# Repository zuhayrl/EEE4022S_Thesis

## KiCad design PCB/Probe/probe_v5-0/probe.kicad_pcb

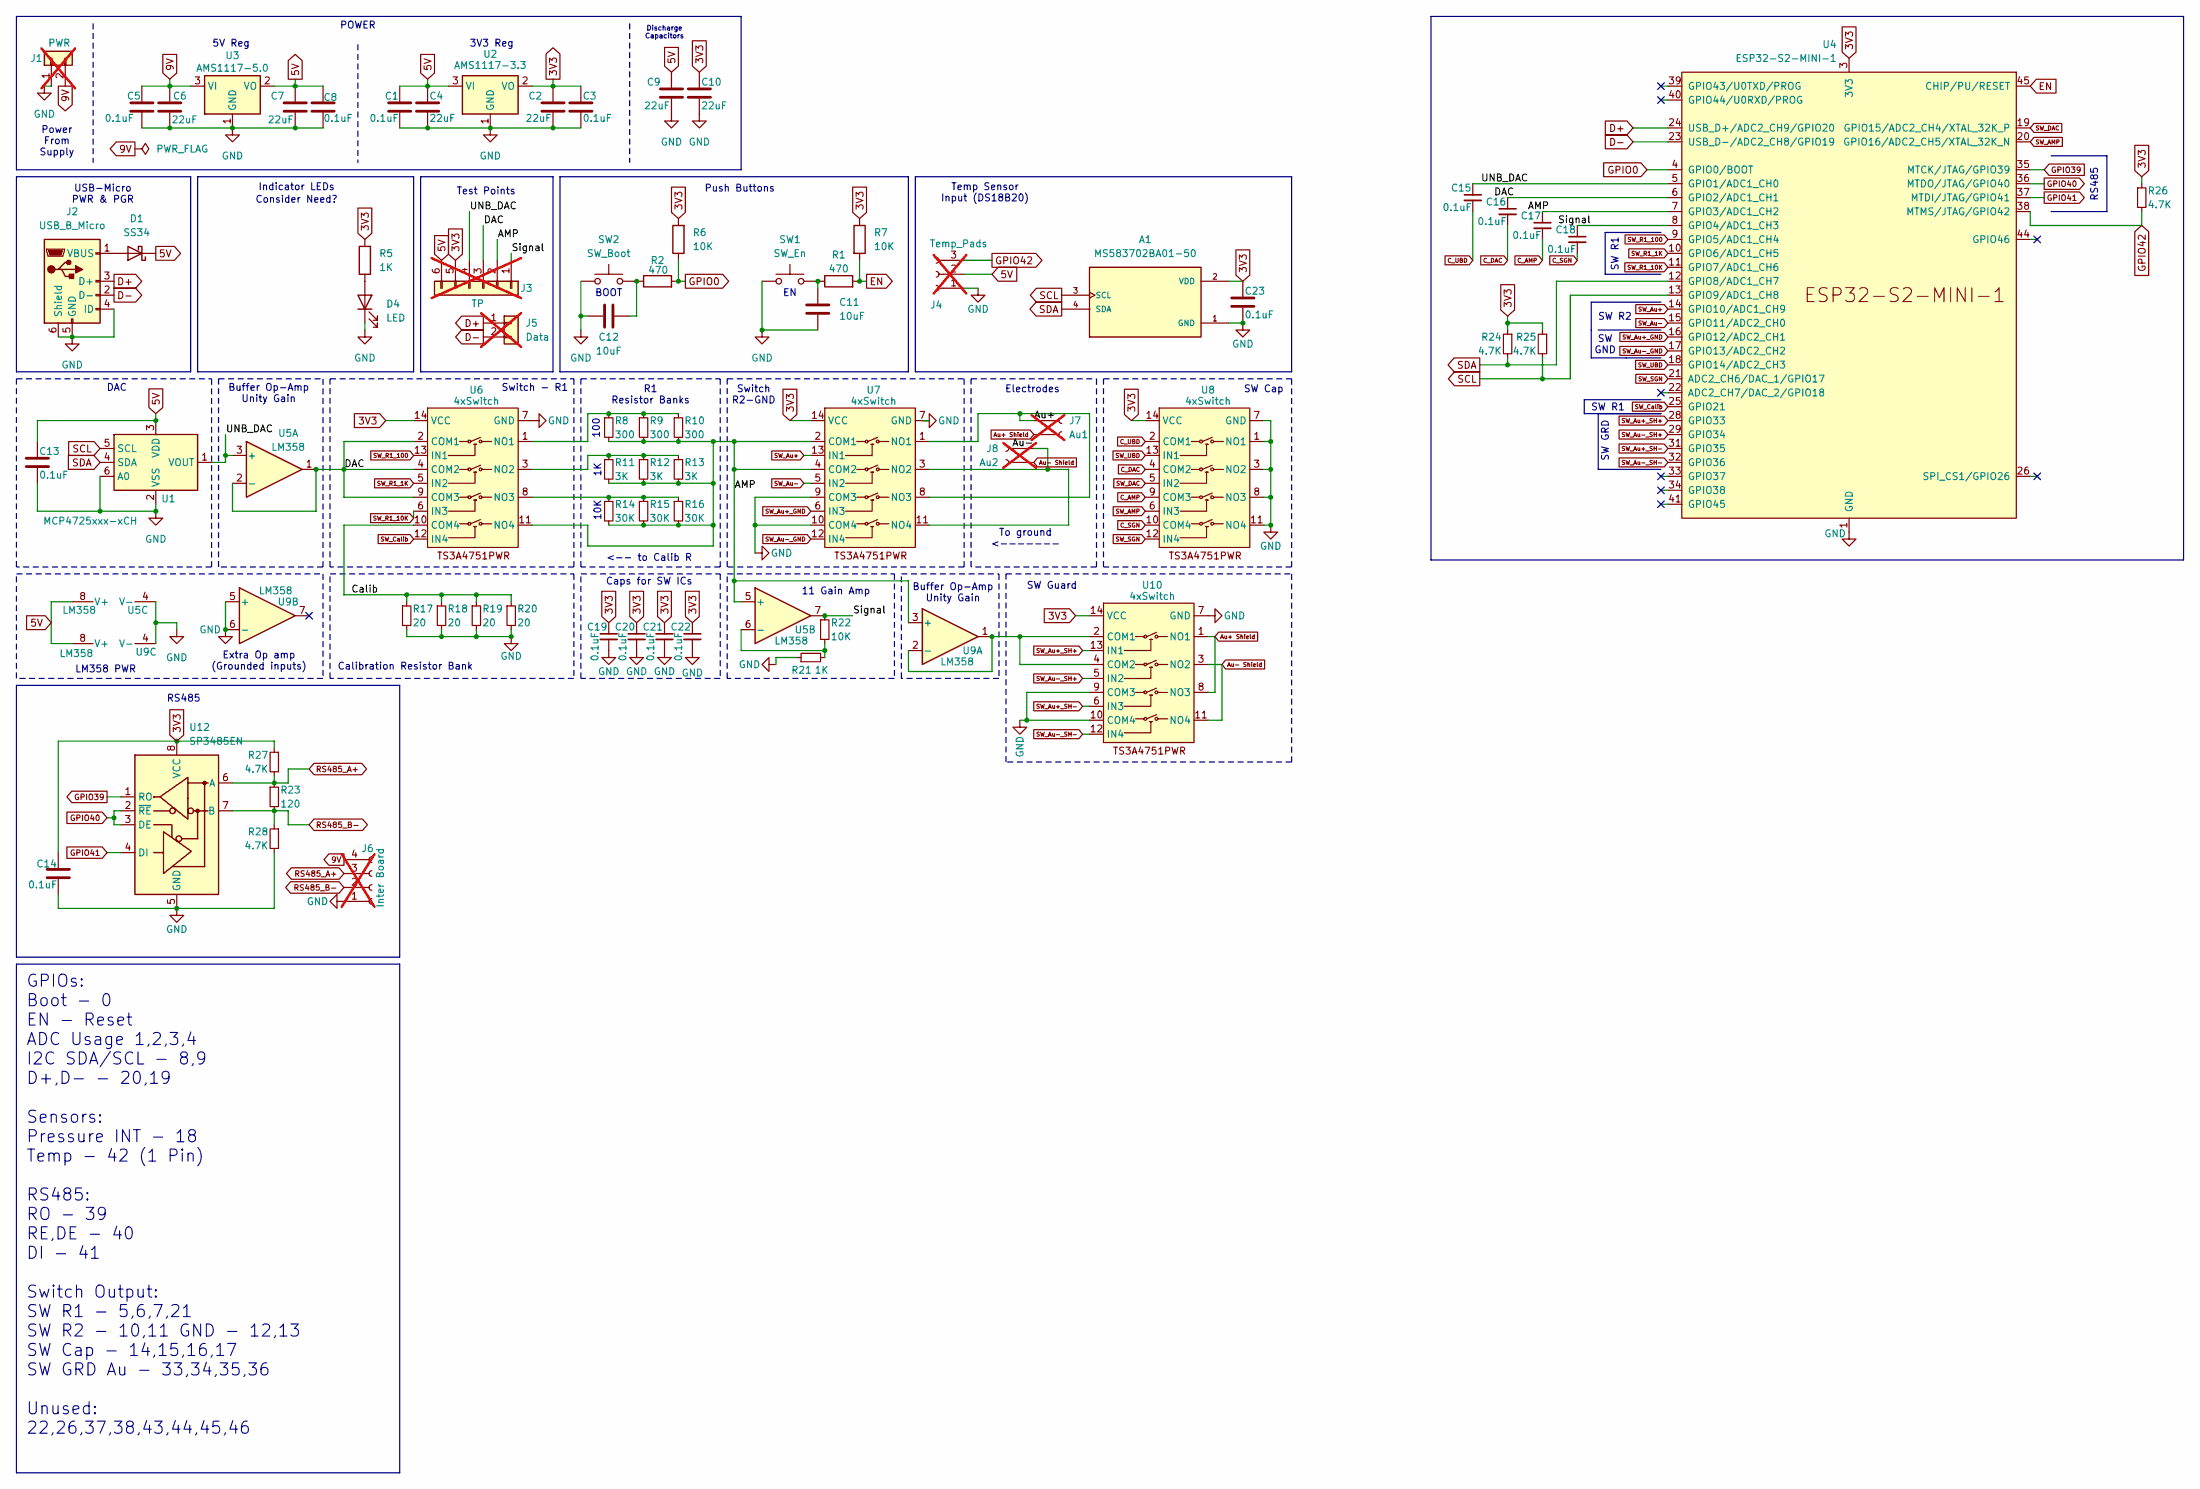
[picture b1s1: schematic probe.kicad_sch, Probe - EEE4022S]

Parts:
A1: MS583702BA01-50; XDCR_MS583702BA01-50; PARTREV A8; JLC Part no. C5785272
C1, C3, C5, C8, C13, C14, C15, C16, C17, C18, C19, C20, C21, C22, C23: 0.1uF; C_0402_1005Metric; JLC Part no. C1525
C2, C4, C6, C7, C9, C10: 22uF; C_1206_3216Metric; JLC Part no. C12891
C11, C12: 10uF; C_0603_1608Metric; JLC Part no. C19702
D1: SS34; D_SMA; JLC Part no. C8678
D4: LED; LED_0603_1608Metric; JLC Part no. C2286
J1: PWR; PinHeader_1x02_P2.54mm_Vertical; not fitted
J2: USB_B_Micro; SHOUHAN_MICROXNJ_Edited; JLC Part no. C404969
J3: TP; PinHeader_1x06_P2.54mm_Vertical; not fitted
J4: Temp_Pads; 3-Wire Solder Pads; not fitted
J5: Data; PinHeader_1x02_P2.54mm_Vertical; not fitted
J6: Inter Board; PinHeader_1x04_P2.54mm_Vertical; not fitted
J7: Au1; Au_Electrode_edited_1; not fitted
J8: Au2; Au_Electrode_edited_1; not fitted
R1, R2: 470; R_0603_1608Metric; JLC Part no. C23179
R5, R21: 1K; R_0603_1608Metric; JLC Part no. C21190
R6, R7, R22: 10K; R_0603_1608Metric; JLC Part no. C25804
R8, R9, R10: 300; R_0603_1608Metric; JLC Part no. C23025
R11, R12, R13: 3K; R_0603_1608Metric; JLC Part no. C4211
R14, R15, R16: 30K; R_0603_1608Metric; JLC Part no. C22984
R17, R18, R19, R20: 20; R_0603_1608Metric; JLC Part no. C22950
R23: 120; R_0603_1608Metric; JLC Part no. C22787
R24, R25, R26, R27, R28: 4.7K; R_0603_1608Metric; JLC Part no. C23162
SW1: SW_En; SW_TS-1088-AR02016; JLC Part no. C720477
SW2: SW_Boot; SW_TS-1088-AR02016; JLC Part no. C720477
U1: MCP4725xxx-xCH; SOT-23-6; JLC Part no. C144198
U2: AMS1117-3.3; SOT-223-3_TabPin2; JLC Part no. C6186
U3: AMS1117-5.0; SOT-223-3_TabPin2; JLC Part no. C6187
U4: ESP32-S2-MINI-1; JLC Part no. C3013906
U5, U9: LM358; SOIC-8_3.9x4.9mm_P1.27mm; JLC Part no. C7950
U6, U7, U8, U10: 4xSwitch; TSSOP-14_4.4x5mm_P0.65mm; JLC Part no. C128399
U12: SP3485EN; SOIC-8_3.9x4.9mm_P1.27mm; JLC Part no. C8963

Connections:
3V3: A1.2 (VDD), C2.1, C3.1, C10.1, C14.1, C19.1, C20.1, C21.1, C22.1, C23.1, J3.5, R5.2, R6.2, R7.1, R24.1, R25.1, R26.1, R27.1, U2.2 (VO), U4.3 (3V3), U6.14 (VCC), U7.14 (VCC), U8.14 (VCC), U10.14 (VCC), U12.8 (VCC)
5V: C1.1, C4.1, C7.1, C8.1, C9.1, C13.1, D1.1 (K), J3.6, J4.2, U1.3 (VDD), U2.3 (VI), U3.2 (VO), U5.8 (V+), U9.8 (V+)
9V: C5.1, C6.1, J1.2, J6.4, U3.3 (VI)
/AMP: C17.1, J3.2, R8.2, R9.2, R10.2, R11.2, R12.2, R13.2, R14.2, R15.2, R16.2, U4.7 (GPIO3/ADC1_CH2), U5.5 (+), U6.11 (NO4), U7.2 (COM1), U7.4 (COM2), U9.3 (+)
/Au+: J7.1, U7.1 (NO1), U7.8 (NO3)
/Au-: J8.1, U7.3 (NO2), U7.11 (NO4)
/Calib: R17.1, R18.1, R19.1, R20.1, U6.10 (COM4)
/DAC: C16.1, J3.3, U4.6 (GPIO2/ADC1_CH1), U5.1, U5.2 (-), U6.2 (COM1), U6.4 (COM2), U6.9 (COM3)
/Signal: C18.1, J3.1, R22.1, U4.8 (GPIO4/ADC1_CH3), U5.7
/UNB_DAC: C15.1, J3.4, U1.1 (VOUT), U4.5 (GPIO1/ADC1_CH0), U5.3 (+)
Au+ Shield: J7.2, U10.1 (NO1), U10.8 (NO3)
Au- Shield: J8.2, U10.3 (NO2), U10.11 (NO4)
C_AMP: C17.2, U8.9 (COM3)
C_DAC: C16.2, U8.4 (COM2)
C_SGN: C18.2, U8.10 (COM4)
C_UBD: C15.2, U8.2 (COM1)
D+: J2.3 (D+), J5.1, U4.24 (USB_D+/ADC2_CH9/GPIO20)
D-: J2.2 (D-), J5.2, U4.23 (USB_D-/ADC2_CH8/GPIO19)
EN: R1.2, R7.2, U4.45 (CHIP/PU/RESET)
GND: A1.1 (GND), C1.2, C2.2, C3.2, C4.2, C5.2, C6.2, C7.2, C8.2, C9.2, C10.2, C11.2, C12.2, C13.2, C14.2, C19.2, C20.2, C21.2, C22.2, C23.2, D4.1 (K), J1.1, J2.4 (ID), J2.5 (GND), J2.6 (Shield), J4.1, J6.1, R17.2, R18.2, R19.2, R20.2, R21.1, R28.2, SW1.1, SW2.1, U1.2 (VSS), U1.6 (A0), U2.1 (GND), U3.1 (GND), U4.1 (GND), U4.2 (GND), U4.30 (GND), U4.42 (GND), U4.43 (GND), U4.46 (GND), U4.47 (GND), U4.48 (GND), U4.49 (GND), U4.50 (GND), U4.51 (GND), U4.52 (GND), U4.53 (GND), U4.54 (GND), U4.55 (GND), U4.56 (GND), U4.57 (GND), U4.58 (GND), U4.59 (GND), U4.60 (GND), U4.61 (GND), U4.62 (GND), U4.63 (GND), U4.64 (GND), U4.65 (GND), U5.4 (V-), U6.7 (GND), U7.7 (GND), U7.9 (COM3), U7.10 (COM4), U8.1 (NO1), U8.3 (NO2), U8.7 (GND), U8.8 (NO3), U8.11 (NO4), U9.4 (V-), U9.5 (+), U9.6 (-), U10.7 (GND), U10.9 (COM3), U10.10 (COM4), U12.5 (GND)
GPIO0: R2.2, R6.1, U4.4 (GPIO0/BOOT)
GPIO39: U4.35 (MTCK/JTAG/GPIO39), U12.1 (RO)
GPIO40: U4.36 (MTDO/JTAG/GPIO40), U12.2 (~RE), U12.3 (DE)
GPIO41: U4.37 (MTDI/JTAG/GPIO41), U12.4 (DI)
GPIO42: J4.3, R26.2, U4.38 (MTMS/JTAG/GPIO42)
unnamed: C11.1, R1.1, SW1.2
unnamed: C12.1, R2.1, SW2.2
unnamed: D1.2 (A), J2.1 (VBUS)
unnamed: D4.2 (A), R5.1
unnamed: R21.2, R22.2, U5.6 (-)
unnamed: R8.1, R9.1, R10.1, U6.1 (NO1)
unnamed: R11.1, R12.1, R13.1, U6.3 (NO2)
unnamed: R14.1, R15.1, R16.1, U6.8 (NO3)
unnamed: U9.1, U9.2 (-), U10.2 (COM1), U10.4 (COM2)
RS485_A+: J6.3, R23.1, R27.2, U12.6 (A)
RS485_B-: J6.2, R23.2, R28.1, U12.7 (B)
SCL: A1.3 (SCL), R25.2, U1.5 (SCL), U4.13 (GPIO9/ADC1_CH8)
SDA: A1.4 (SDA), R24.2, U1.4 (SDA), U4.12 (GPIO8/ADC1_CH7)
SW_AMP: U4.20 (GPIO16/ADC2_CH5/XTAL_32K_N), U8.6 (IN3)
SW_Au+: U4.14 (GPIO10/ADC1_CH9), U7.13 (IN1)
SW_Au+_GND: U4.16 (GPIO12/ADC2_CH1), U7.6 (IN3)
SW_Au+_SH+: U4.28 (GPIO33), U10.13 (IN1)
SW_Au+_SH-: U4.31 (GPIO35), U10.6 (IN3)
SW_Au-: U4.15 (GPIO11/ADC2_CH0), U7.5 (IN2)
SW_Au-_GND: U4.17 (GPIO13/ADC2_CH2), U7.12 (IN4)
SW_Au-_SH+: U4.29 (GPIO34), U10.5 (IN2)
SW_Au-_SH-: U4.32 (GPIO36), U10.12 (IN4)
SW_Calib: U4.25 (GPIO21), U6.12 (IN4)
SW_DAC: U4.19 (GPIO15/ADC2_CH4/XTAL_32K_P), U8.5 (IN2)
SW_R1_1K: U4.10 (GPIO6/ADC1_CH5), U6.5 (IN2)
SW_R1_10K: U4.11 (GPIO7/ADC1_CH6), U6.6 (IN3)
SW_R1_100: U4.9 (GPIO5/ADC1_CH4), U6.13 (IN1)
SW_SGN: U4.21 (ADC2_CH6/DAC_1/GPIO17), U8.12 (IN4)
SW_UBD: U4.18 (GPIO14/ADC2_CH3), U8.13 (IN1)

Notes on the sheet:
GPIOs: Boot - 0 EN - Reset ADC Usage 1,2,3,4 I2C SDA/SCL - 8,9 D+,D- - 20,19 Sensors: Pressure INT - 18 Temp - 42 (1 Pin) RS485: RO - 39 RE,DE - 40 DI - 41 Switch Output: SW R1 - 5,6,7,21 SW R2 - 10,11 GND - 12,13 SW Cap - 14,15,16,17 SW GRD Au - 33,34,35,36 Unused: 22,26,37,38,43,44,45,46
Extra Op amp (Grounded inputs)
Switch - R1
Calibration Resistor Bank
BOOT
SW R1
Test Points
5V Reg
POWER
SW GND
Discharge Capacitors
SW Cap
3V3 Reg
LM358 PWR
USB-Micro PWR & PGR
To ground <-------
Push Buttons
SW R2
DAC
Consider Need?
10K
SW GRD
Electrodes
RS485
Buffer Op-Amp Unity Gain
Temp Sensor Input (DS18B20)
100
Indicator LEDs
Switch R2-GND
SW Guard
Caps for SW ICs
<-- to Calib R
Power From Supply
11 Gain Amp
R1 Resistor Banks

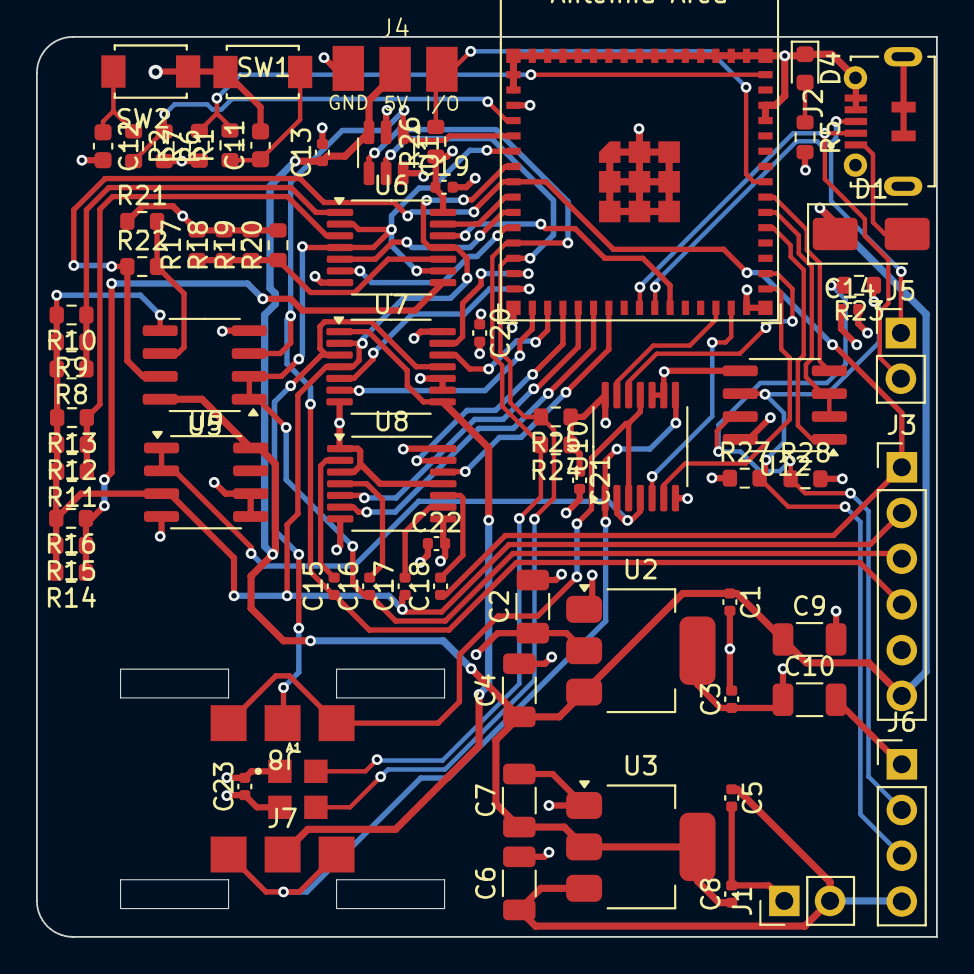
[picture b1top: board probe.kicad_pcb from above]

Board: 4 copper layers, 50.0 x 50.0 mm, 73 parts (0 on the bottom side), 54 nets.

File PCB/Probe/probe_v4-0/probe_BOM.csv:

Comment,Designator,Footprint,JLC Part #
0.1uF,"C1,C3,C5,C8,C13,C14,C15,C16,C17,C18,C19,C20,C21,C22,C23",Capacitor_SMD:C_0402_1005Metric,C1525
22uF,"C2,C4,C6,C7,C9,C10",Capacitor_SMD:C_1206_3216Metric,C12891
10uF,"C11,C12",Capacitor_SMD:C_0603_1608Metric,C19702
SS34,D1,Diode_SMD:D_SMA,C8678
LED,D4,LED_SMD:LED_0603_1608Metric,C2286
PWR,J1,Connector_PinHeader_2.54mm:PinHeader_1x02_P2.54mm_Vertical,
USB_B_Micro,J2,ThesisLib:SHOUHAN_MICROXNJ_Edited,C404969
TP,J3,Connector_PinHeader_2.54mm:PinHeader_1x06_P2.54mm_Vertical,
Temp_Pads,J4,ThesisLib:3-Wire Solder Pads,
Data,J5,Connector_PinHeader_2.54mm:PinHeader_1x02_P2.54mm_Vertical,
Inter Board,J6,Connector_PinHeader_2.54mm:PinHeader_1x04_P2.54mm_Vertical,
Au1,J7,ThesisLib:Au_Electrode_edited_1,
Au2,J8,ThesisLib:Au_Electrode_edited_1,
470,"R1,R2",Resistor_SMD:R_0603_1608Metric,
1K,"R5,R21",Resistor_SMD:R_0603_1608Metric,C21190
10K,"R6,R7,R22",Resistor_SMD:R_0603_1608Metric,C25804
300,"R8,R9,R10",Resistor_SMD:R_0603_1608Metric,C23025
3K,"R11,R12,R13",Resistor_SMD:R_0603_1608Metric,C4211
30K,"R14,R15,R16",Resistor_SMD:R_0603_1608Metric,C22984
20,"R17,R18,R19,R20",Resistor_SMD:R_0603_1608Metric,C22950
120,R23,Resistor_SMD:R_0603_1608Metric,C22787
4.7K,"R24,R25,R26,R27,R28",Resistor_SMD:R_0603_1608Metric,C23162
SW_En,SW1,ThesisLib:SW_TS-1088-AR02016,C720477
SW_Boot,SW2,ThesisLib:SW_TS-1088-AR02016,C720477
MCP4725xxx-xCH,U1,Package_TO_SOT_SMD:SOT-23-6,C144198
AMS1117-3.3,U2,Package_TO_SOT_SMD:SOT-223-3_TabPin2,C6186
AMS1117-5.0,U3,Package_TO_SOT_SMD:SOT-223-3_TabPin2,C6187
ESP32-S2-MINI-1,U4,PCM_Espressif:ESP32-S2-MINI-1,C3013906
LM358,"U5,U9",Package_SO:SOIC-8_3.9x4.9mm_P1.27mm,C7950
4xSwitch,"U6,U7,U8,U10",Package_SO:TSSOP-14_4.4x5mm_P0.65mm,C128399
SP3485EN,U12,Package_SO:SOIC-8_3.9x4.9mm_P1.27mm,C8963
LPS28DFW,U13,ThesisLib:CCLGA-7L,C3263277

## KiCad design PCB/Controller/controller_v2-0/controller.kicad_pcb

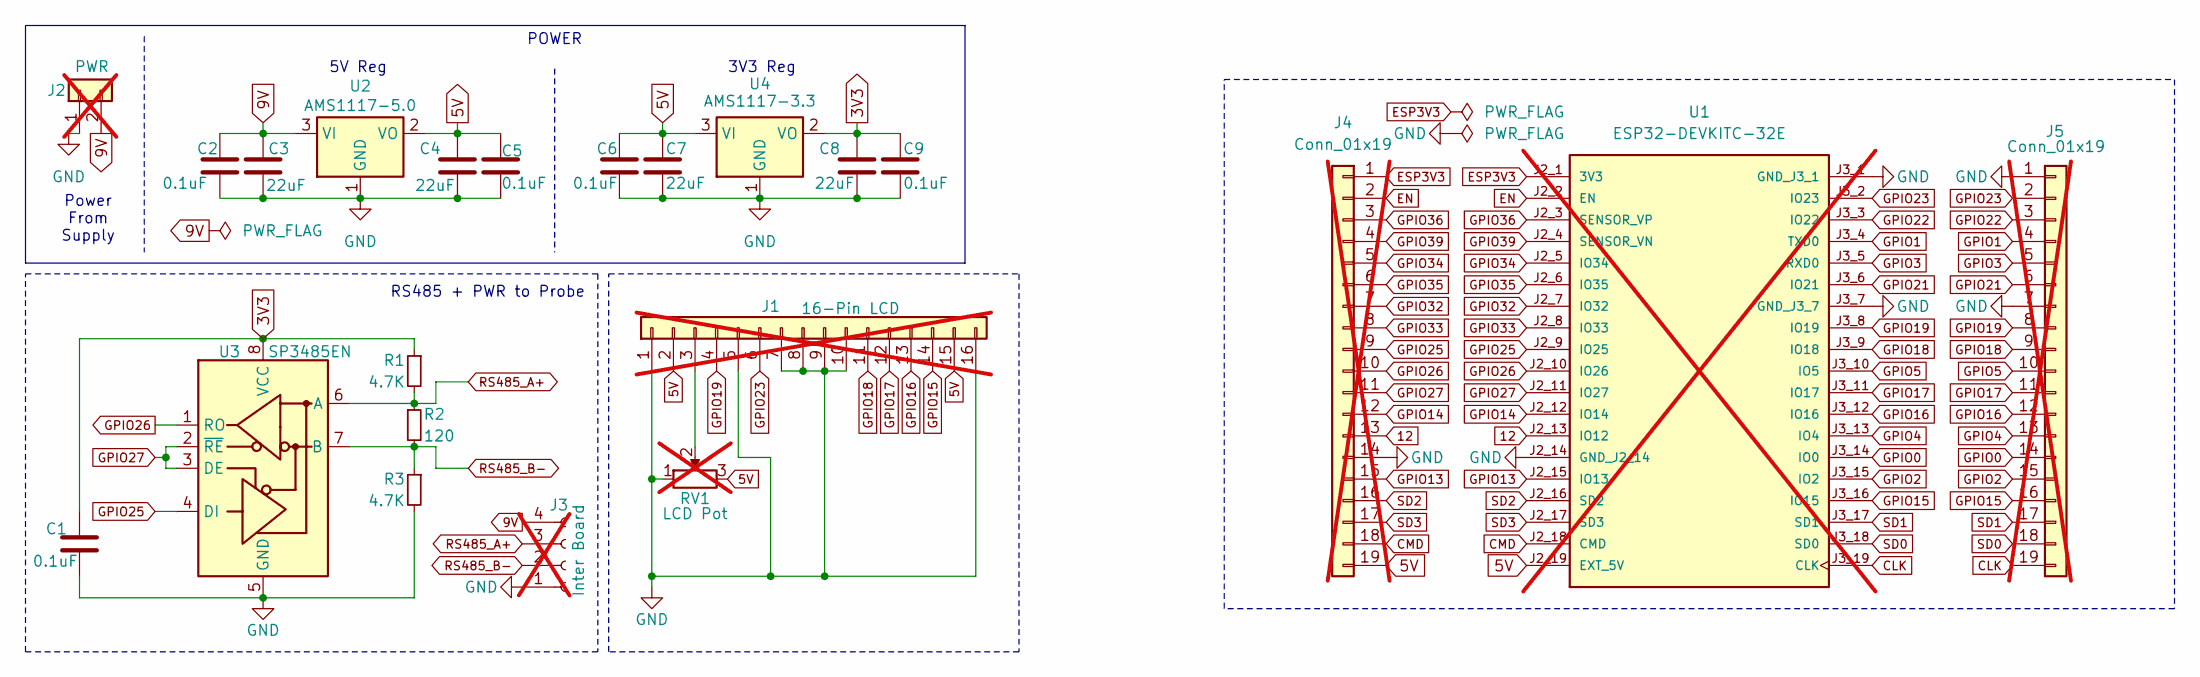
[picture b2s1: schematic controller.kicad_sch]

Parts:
C1, C2, C5, C6, C9: 0.1uF; C_0402_1005Metric; JLCPCB Part No. C1525
C3, C4, C7, C8: 22uF; C_1206_3216Metric; JLCPCB Part No. C12891
J1: 16-Pin LCD; PinSocket_1x16_P2.54mm_Vertical; not fitted
J2: PWR; PinHeader_1x02_P2.54mm_Vertical; not fitted
J3: Inter Board; PinHeader_1x04_P2.54mm_Vertical; not fitted
J4, J5: Conn_01x19; PinHeader_1x19_P2.54mm_Vertical; not fitted
R1, R3: 4.7K; R_0603_1608Metric; JLCPCB Part No. C23162
R2: 120; R_0603_1608Metric; JLCPCB Part No. C22787
RV1: LCD Pot; 10KPot; not fitted
U1: ESP32-DEVKITC-32E; MODULE_ESP32-DEVKITC-32E-Edited2; PARTREV 1.4; not fitted
U2: AMS1117-5.0; SOT-223-3_TabPin2; JLCPCB Part No. C6187
U3: SP3485EN; SOIC-8_3.9x4.9mm_P1.27mm; JLCPCB Part No. C8963
U4: AMS1117-3.3; SOT-223-3_TabPin2; JLCPCB Part No. C6186

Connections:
3V3: C1.1, C8.1, C9.1, R1.1, U3.8 (VCC), U4.2 (VO)
5V: C4.1, C5.1, C6.1, C7.1, J1.2, J1.15, J4.19, RV1.3, U1.J2_19 (EXT_5V), U2.2 (VO), U4.3 (VI)
9V: C2.1, C3.1, J2.2, J3.4, U2.3 (VI)
12: J4.13, U1.J2_13 (IO12)
CLK: J5.19, U1.J3_19 (CLK)
CMD: J4.18, U1.J2_18 (CMD)
EN: J4.2, U1.J2_2 (EN)
ESP3V3: J4.1, U1.J2_1 (3V3)
GND: C1.2, C2.2, C3.2, C4.2, C5.2, C6.2, C7.2, C8.2, C9.2, J1.1, J1.5, J1.7, J1.8, J1.9, J1.10, J1.16, J2.1, J3.1, J4.14, J5.1, J5.7, R3.2, RV1.1, U1.J2_14 (GND_J2_14), U1.J3_1 (GND_J3_1), U1.J3_7 (GND_J3_7), U2.1 (GND), U3.5 (GND), U4.1 (GND)
GPIO0: J5.14, U1.J3_14 (IO0)
GPIO1: J5.4, U1.J3_4 (TXD0)
GPIO2: J5.15, U1.J3_15 (IO2)
GPIO3: J5.5, U1.J3_5 (RXD0)
GPIO4: J5.13, U1.J3_13 (IO4)
GPIO5: J5.10, U1.J3_10 (IO5)
GPIO13: J4.15, U1.J2_15 (IO13)
GPIO14: J4.12, U1.J2_12 (IO14)
GPIO15: J1.14, J5.16, U1.J3_16 (IO15)
GPIO16: J1.13, J5.12, U1.J3_12 (IO16)
GPIO17: J1.12, J5.11, U1.J3_11 (IO17)
GPIO18: J1.11, J5.9, U1.J3_9 (IO18)
GPIO19: J1.4, J5.8, U1.J3_8 (IO19)
GPIO21: J5.6, U1.J3_6 (IO21)
GPIO22: J5.3, U1.J3_3 (IO22)
GPIO23: J1.6, J5.2, U1.J3_2 (IO23)
GPIO25: J4.9, U1.J2_9 (IO25), U3.4 (DI)
GPIO26: J4.10, U1.J2_10 (IO26), U3.1 (RO)
GPIO27: J4.11, U1.J2_11 (IO27), U3.2 (~RE), U3.3 (DE)
GPIO32: J4.7, U1.J2_7 (IO32)
GPIO33: J4.8, U1.J2_8 (IO33)
GPIO34: J4.5, U1.J2_5 (IO34)
GPIO35: J4.6, U1.J2_6 (IO35)
GPIO36: J4.3, U1.J2_3 (SENSOR_VP)
GPIO39: J4.4, U1.J2_4 (SENSOR_VN)
unnamed: J1.3, RV1.2
RS485_A+: J3.3, R1.2, R2.1, U3.6 (A)
RS485_B-: J3.2, R2.2, R3.1, U3.7 (B)
SD0: J5.18, U1.J3_18 (SD0)
SD1: J5.17, U1.J3_17 (SD1)
SD2: J4.16, U1.J2_16 (SD2)
SD3: J4.17, U1.J2_17 (SD3)

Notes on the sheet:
5V Reg
RS485 + PWR to Probe
Power From Supply
POWER
3V3 Reg

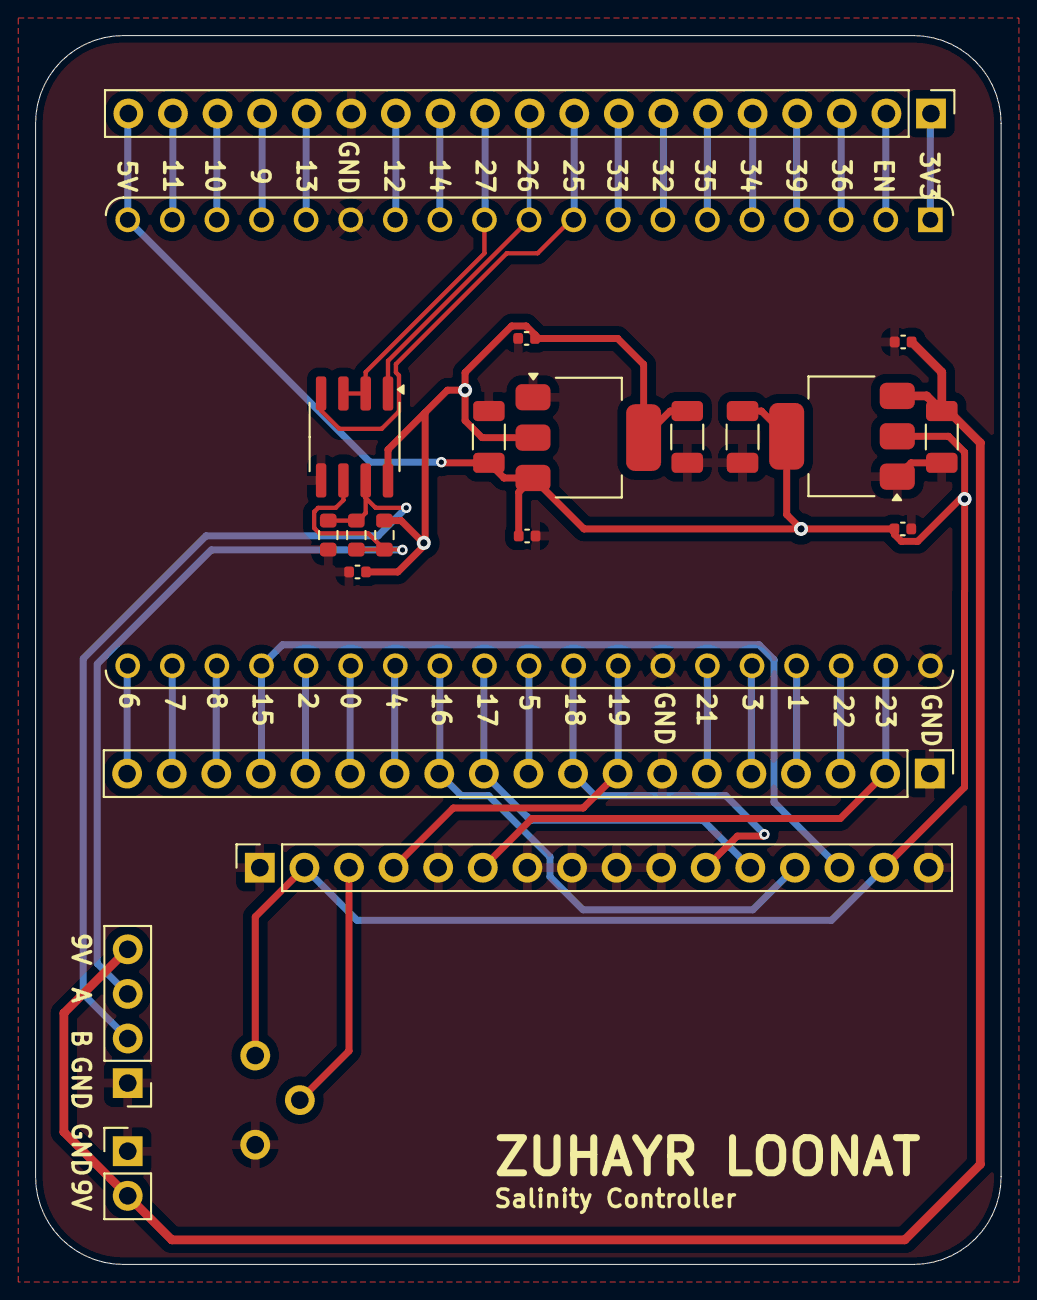
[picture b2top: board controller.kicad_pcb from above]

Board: 2 copper layers, 55.0 x 70.0 mm, 22 parts (0 on the bottom side), 41 nets.

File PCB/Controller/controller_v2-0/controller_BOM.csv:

Comment,Designator,Footprint,JLCPCB Part #
0.1uF,"C1,C2,C5,C6,C9",Capacitor_SMD:C_0402_1005Metric,C1525
22uF,"C3,C4,C7,C8",Capacitor_SMD:C_1206_3216Metric,C12891
16-Pin LCD,J1,Connector_PinSocket_2.54mm:PinSocket_1x16_P2.54mm_Vertical,
PWR,J2,Connector_PinHeader_2.54mm:PinHeader_1x02_P2.54mm_Vertical,
Inter Board,J3,Connector_PinHeader_2.54mm:PinHeader_1x04_P2.54mm_Vertical,
Conn_01x19,"J4,J5",Connector_PinHeader_2.54mm:PinHeader_1x19_P2.54mm_Vertical,
4.7K,"R1,R3",Resistor_SMD:R_0603_1608Metric,C23162
120,R2,Resistor_SMD:R_0603_1608Metric,C22787
LCD Pot,RV1,ThesisLib:10KPot,
ESP32-DEVKITC-32E,U1,ThesisLib:MODULE_ESP32-DEVKITC-32E-Edited2,
AMS1117-5.0,U2,Package_TO_SOT_SMD:SOT-223-3_TabPin2,C6187
SP3485EN,U3,Package_SO:SOIC-8_3.9x4.9mm_P1.27mm,C8963
AMS1117-3.3,U4,Package_TO_SOT_SMD:SOT-223-3_TabPin2,C6186

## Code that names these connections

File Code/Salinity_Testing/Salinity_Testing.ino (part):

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#define DAC_MAX_3V3 2200  // Limit for 3V out when powered at 5V

// ADC Inputs
#define ADC_UNB 1         // ADC input from unbiased DAC (before op-amp)
#define ADC_DAC 2         // ADC input from op amp after DAC
#define ADC_AMP 3         // ADC input over R2 before 11x op-amp
#define ADC_SGN 4         // ADC input from ampl (drop of R2) after 11x op amp

// Switch for Caps by ADCs
#define SW_UNB 14         // ADC IO 1 Switch UNB
#define SW_DAC 15         // ADC IO 2 Switch DAC
#define SW_AMP 16         // ADC IO 3 Switch AMP
#define SW_SGN 17         // ADC IO 4 Switch SGN

// Switch for R1 Cap
#define SW_R1_100 5       // R1 - 100 Ohm switch
#define SW_R1_1K  6       // R1 - 1K Ohm Switch
#define SW_R1_10K 7       // R1 - 10K ohm Switch
#define SW_Calib 21       // Calibration Resistor switch

// Switch for choosing probe
#define SW_AuP     10     // SW_Au+
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// ===== SETUP ===============================================================================================
void setup() {
  Serial.begin(115200);
  Wire.begin(8, 9);  // SDA=GPIO8, SCL=GPIO9 for I2C
  Wire.setClock(400000); //set dac to fast mode

  // Initialize MS5837 Pressure Sensor
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
  // --- Switches ---
  // R1 & Calib
  pinMode(SW_R1_100, OUTPUT);
  pinMode(SW_R1_1K, OUTPUT);
  pinMode(SW_R1_10K, OUTPUT);
  pinMode(SW_Calib, OUTPUT);
  // ADC
  pinMode(SW_UNB, OUTPUT);
  pinMode(SW_DAC, OUTPUT);
  pinMode(SW_AMP, OUTPUT);
  pinMode(SW_SGN, OUTPUT);
  //digitalWrite(SW_UNB, HIGH);
  //digitalWrite(SW_DAC, HIGH);
  //digitalWrite(SW_AMP, HIGH);
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// ===== get voltage over probes at a point =====================================================
void pointVoltage(float voltage, int r1){
  printBoth("PV: FWD, BCK, CLF:");
  int r1pins[] = {SW_R1_100, SW_R1_1K, SW_R1_10K};
  float r1Resistances[] = {100, 1000, 10000};
  int dacVal = (int)((voltage / 5) * 4095); // scale 0–5V to 0–4095

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// ===== get calib factor =======================================================================
float calibFactor(float voltage, int r1){
  printBoth("Calib Factor:");
  int r1pins[] = {SW_R1_100, SW_R1_1K, SW_R1_10K};
  float r1Resistances[] = {100, 1000, 10000};
  float res = r1Resistances[r1];
  int dacVal = (int)((voltage / 5) * 4095); // scale 0–5V to 0–4095
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void sweepVoltage(int r1, int probe){
  printBoth("Voltage Sweep");
  printBoth(String(calibFactor(1.5, 0)));
  int r1pins[] = {SW_R1_100, SW_R1_1K, SW_R1_10K};
  digitalWrite(r1pins[r1],HIGH); // turn on chosen R1 resistor
  if (probe==0){posProbe(1);}else{negProbe(1);}
  for (int i=0; i<=20; i++){ // 0-2.5V
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
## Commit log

2025-08-08 Add initial LaTeX report template and content
    Added the initial structure for the final report, including LaTeX source files for Introduction, Literature Review, Methodology, Results, Discussion, Conclusions, Recommendations, References, and app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
2025-08-08 Restructure report: move files into Body and Appendix
    Moved main report sections and appendices into 'Body' and 'Appendix' subdirectories for improved organization. Updated image reference in Literature.tex to reflect new path. Removed old auxiliary and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
2025-08-08 Add final report files and update structure
    - Created Main.out and Main.toc for bookmarks and table of contents.
    - Updated Main.pdf with minor text corrections in the Literature Review section.
    - Modified Main.tex to adjust image path, change font sizes for headings, and update bibliography inclusion.
    - Removed obsolete auxiliary files for Methodology, Recommendations, Results, and appendices.
    - Added new References files in the Referencing folder with proper citations.
    - Created README.md to outline the project structure and guidelines for thesis formatting.
2025-08-08 Update LaTeX files: fix spacing in department name and regenerate auxiliary files
2025-08-08 Update LaTeX files: correct spacing, enhance formatting, and regenerate output files
2025-08-08 Fixed Formatting Issues in Main.tex and Craeted folder structure and relevant readme files
2025-08-09 Refactor FinalReport: Update document structure and content
    - Removed redundant figure inputs from Main.fls.
    - Updated font inputs in Main.fls to include additional fonts.
    - Adjusted timestamps in Main.log to reflect the latest compilation date.
    - Modified bookmarks in Main.out to reflect new chapter structure.
    - Updated the date in the title page of Main.pdf to August 9, 2025.
    - Added a glossary section in Main.tex with relevant symbols and descriptions.
2025-08-11 Add ADC_DAC_Test example: Implement LED control and DAC output with serial monitoring
2025-08-14 Created Probe PCB
2025-08-14 renamed file
2025-08-16 Probe-Schematic editing
2025-08-17 Updated PCB
    Added Measuring Circuitry
2025-08-18 small probe pcb updates
2025-08-19 Created PCB and New Schematic Version
2025-08-19 Added ML folder
2025-08-22 All PCBs Done
2025-08-24 Created BOMs
2025-08-25 Gerbers and BOMS
2025-08-26 BOM, Pos, Gerbers Redone
2025-08-28 Order Ready Finally
2025-09-23 added ga form
2025-09-24 started coding probe pcb
2025-09-27 Refactor code structure for improved readability and maintainability
2025-09-27 Created Calibration test Code
2025-09-27 Started work on calibration code
2025-09-27 adding adc code
2025-09-28 Created Readme for the adc functionality and added corresponding code
2025-09-28 added functions for rs485
2025-09-28 code neatening
2025-09-28 created seperate files for I2C functions
2025-09-28 added files for dac functions
2025-09-28 added files for adc functions
2025-09-28 added files for rs485 functions and fixed mistakes in other header files
2025-09-28 updated main to use added function header files
2025-09-29 chnaged monitor speed
2025-10-09 ga forms
2025-10-12 added driver headers
2025-10-13 Update Final Report: Revise bookmarks, update submission date, enhance literature review, and add glossary
    - Revised bookmarks in Main.out for improved navigation and clarity.
    - Updated submission date in Main.pdf from August 9, 2025, to October 13, 2025.
    - Enhanced the literature review section in Main.pdf to include detailed discussions on salinity measurement technologies and methodologies.
    - Removed the glossary section from Main.tex and integrated a new glossary using the glossaries-extra package.
    - Added glossary definitions for key physical quantities, constants, and acronyms in glossary.tex.
    - Updated references in References.bib to include new sources related to salinity and oceanog
2025-10-13 rewriting lit review into main doc
2025-10-19 progress with conductivity
2025-10-19 Started Voltage Testing
2025-10-21 added to doc
2025-10-22 updates to doc
2025-10-22 update docs
2025-10-23 doc chnages
2025-10-23 completed lit review rewrite
2025-10-23 added pictures
2025-10-24 progress on report
2025-10-25 box box box box
2025-10-25 last push
2025-10-26 just ac testing left
2025-10-27 its hammer time
2025-10-27 Finish Line
